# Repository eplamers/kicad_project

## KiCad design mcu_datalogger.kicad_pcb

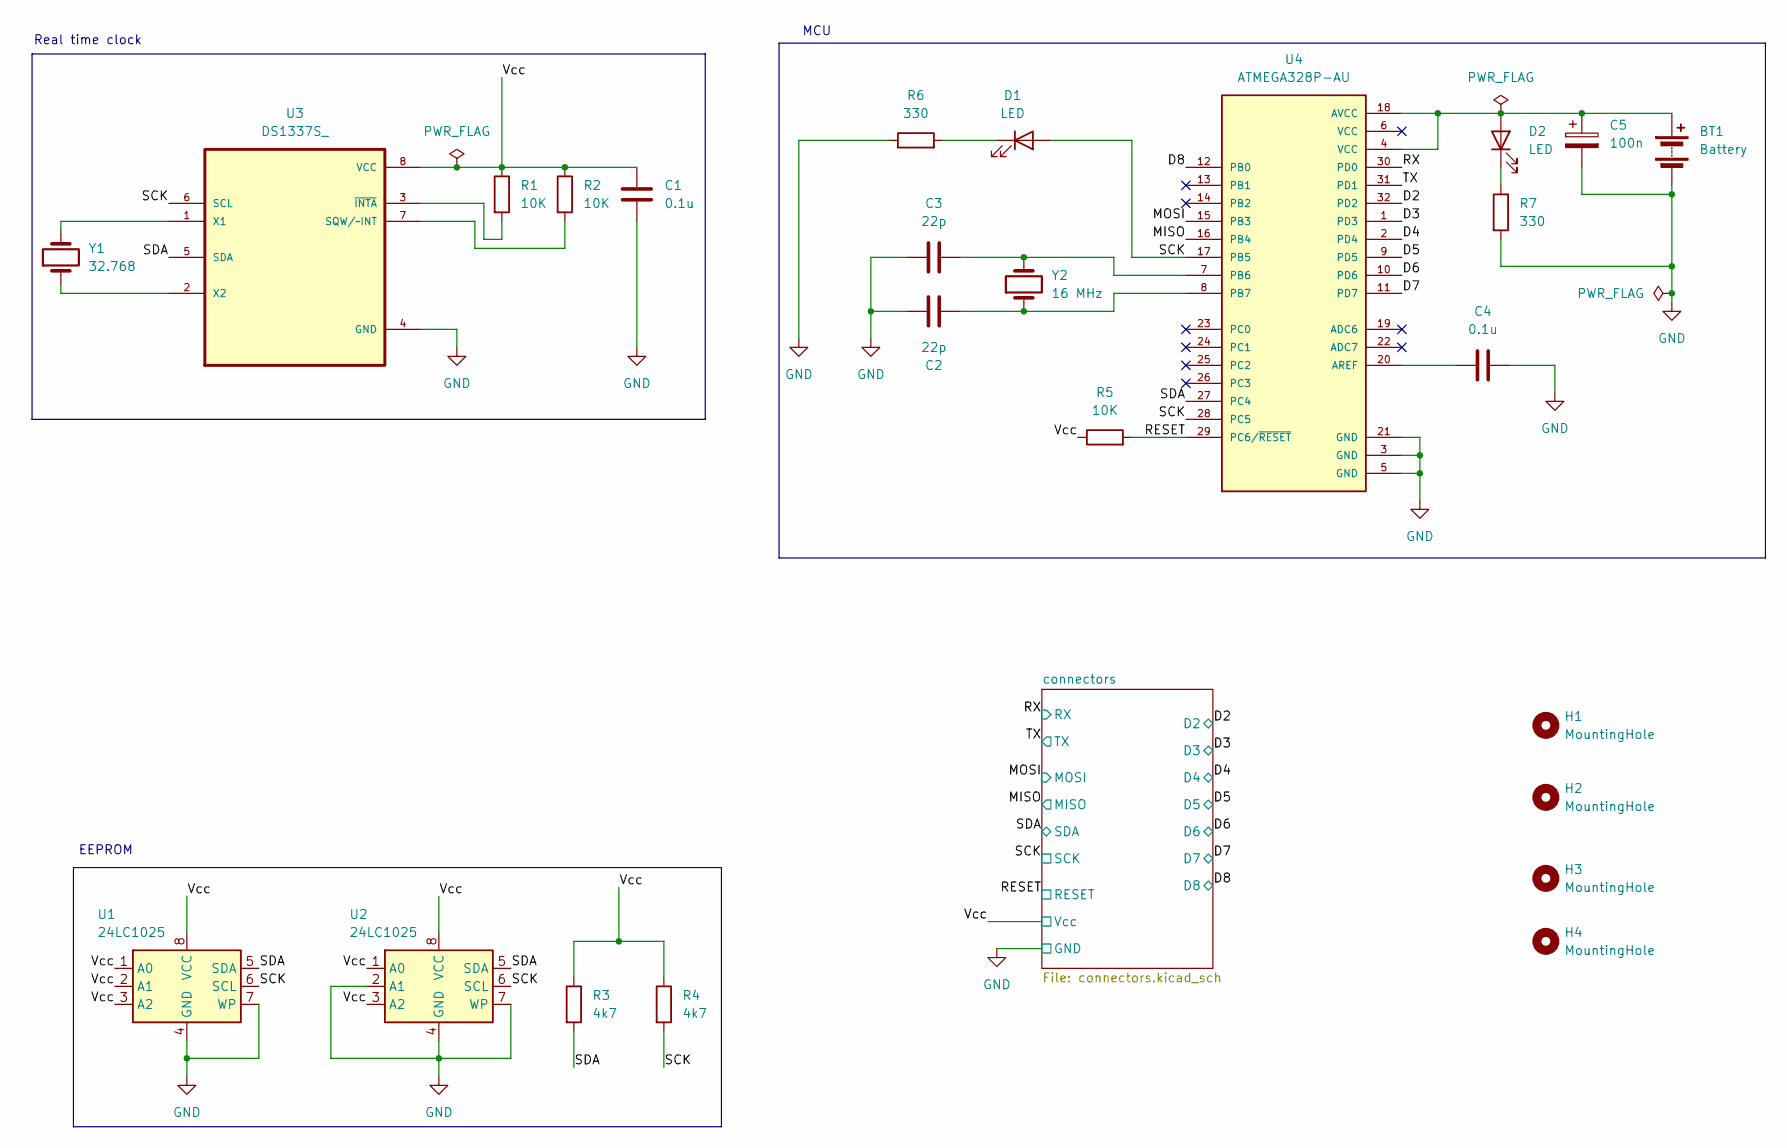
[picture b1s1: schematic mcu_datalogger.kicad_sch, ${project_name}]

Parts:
BT1: Battery; PinHeader_1x02_P2.54mm_Horizontal
C1, C4: 0.1u; C_0805_2012Metric
C2, C3: 22p; C_0805_2012Metric
C5: 100n; C_0805_2012Metric
D1, D2: LED; LED_0805_2012Metric
H1, H2, H3, H4: MountingHole; MountingHole_2.2mm_M2
R1, R2, R5: 10K; R_0805_2012Metric
R3, R4: 4k7; R_0805_2012Metric
R6, R7: 330; R_0805_2012Metric
U1, U2: 24LC1025; SOIC-8_5.3x5.3mm_P1.27mm
U3: DS1337S_; SOIC127P600X175-8N
U4: ATMEGA328P-AU; QFP80P900X900X120-32N; PARTREV 8271A
Y1: 32.768; Crystal_SMD_5032-2Pin_5.0x3.2mm_HandSoldering
Y2: 16 MHz; Crystal_SMD_5032-2Pin_5.0x3.2mm_HandSoldering

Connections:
/D2: U4.32 (PD2); also elsewhere on the board
/D3: U4.1 (PD3); also elsewhere on the board
/D4: U4.2 (PD4); also elsewhere on the board
/D5: U4.9 (PD5); also elsewhere on the board
/D6: U4.10 (PD6); also elsewhere on the board
/D7: U4.11 (PD7); also elsewhere on the board
/D8: U4.12 (PB0); also elsewhere on the board
/MISO: U4.16 (PB4); also elsewhere on the board
/MOSI: U4.15 (PB3); also elsewhere on the board
/RESET: R5.2, U4.29 (PC6/~RESET); also elsewhere on the board
/RX: U4.30 (PD0); also elsewhere on the board
/SCK: D1.2 (A), R4.2, U1.6 (SCL), U2.6 (SCL), U3.6 (SCL), U4.17 (PB5), U4.28 (PC5); also elsewhere on the board
/SDA: R3.2, U1.5 (SDA), U2.5 (SDA), U3.5 (SDA), U4.27 (PC4); also elsewhere on the board
/TX: U4.31 (PD1); also elsewhere on the board
/Vcc: C1.1, R1.1, R2.1, R3.1, R4.1, R5.1, U1.1 (A0), U1.2 (A1), U1.3 (A2), U1.8 (VCC), U2.1 (A0), U2.3 (A2), U2.8 (VCC), U3.8 (VCC); also elsewhere on the board
GND: BT1.2 (-), C1.2, C2.1, C3.1, C4.2, C5.2, R6.1, R7.2, U1.4 (GND), U1.7 (WP), U2.2 (A1), U2.4 (GND), U2.7 (WP), U3.4 (GND), U4.3 (GND), U4.5 (GND), U4.21 (GND); also elsewhere on the board
unnamed: BT1.1 (+), C5.1, D2.2 (A), U4.4 (VCC), U4.18 (AVCC)
unnamed: D1.1 (K), R6.2
unnamed: D2.1 (K), R7.1
unnamed: R2.2, U3.7 (SQW/~INT)
unnamed: U3.1 (X1), Y1.2
unnamed: U3.2 (X2), Y1.1
unnamed: R1.2, U3.3 (~INTA)
unnamed: C4.1, U4.20 (AREF)
unnamed: C3.2, U4.7 (PB6), Y2.2
unnamed: C2.2, U4.8 (PB7), Y2.1

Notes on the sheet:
MCU
EEPROM
Real time clock

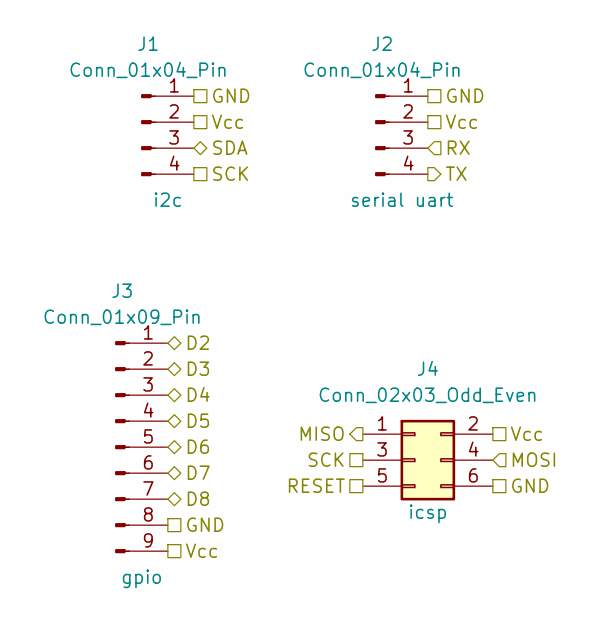
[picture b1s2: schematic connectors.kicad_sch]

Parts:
J1, J2: Conn_01x04_Pin; PinHeader_1x04_P2.54mm_Vertical
J3: Conn_01x09_Pin; PinHeader_1x09_P2.54mm_Vertical
J4: Conn_02x03_Odd_Even; PinHeader_2x03_P2.54mm_Vertical

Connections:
/D2: J3.1; also elsewhere on the board
/D3: J3.2; also elsewhere on the board
/D4: J3.3; also elsewhere on the board
/D5: J3.4; also elsewhere on the board
/D6: J3.5; also elsewhere on the board
/D7: J3.6; also elsewhere on the board
/D8: J3.7; also elsewhere on the board
/MISO: J4.1; also elsewhere on the board
/MOSI: J4.4; also elsewhere on the board
/RESET: J4.5; also elsewhere on the board
/RX: J2.3; also elsewhere on the board
/SCK: J1.4, J4.3; also elsewhere on the board
/SDA: J1.3; also elsewhere on the board
/TX: J2.4; also elsewhere on the board
/Vcc: J1.2, J2.2, J3.9, J4.2; also elsewhere on the board
GND: J1.1, J2.1, J3.8, J4.6; also elsewhere on the board

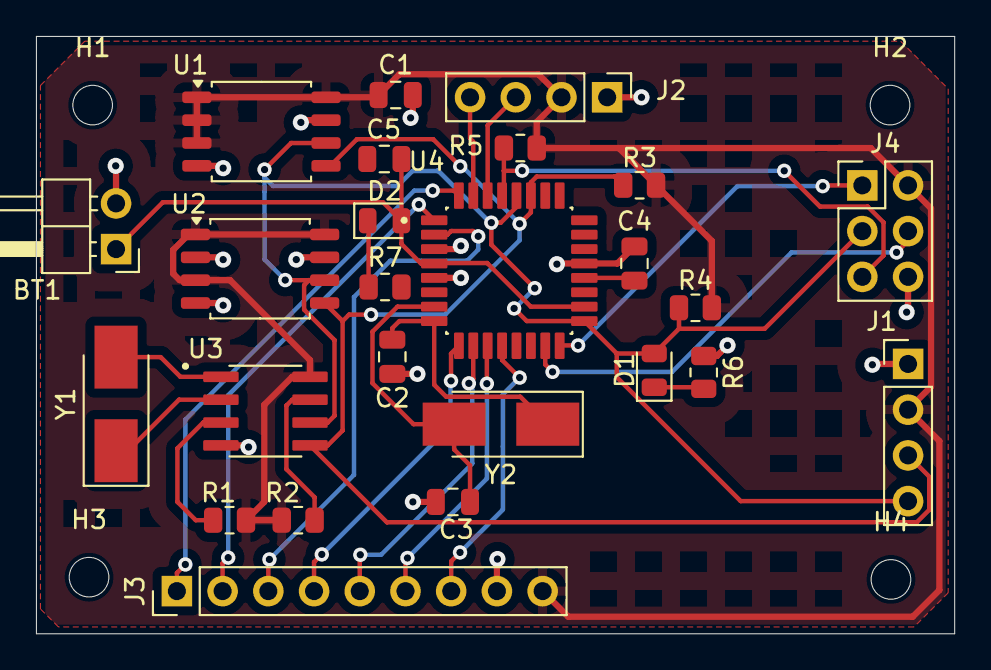
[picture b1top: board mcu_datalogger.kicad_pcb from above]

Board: 2 copper layers, 51.0 x 33.2 mm, 29 parts (0 on the bottom side), 26 nets.

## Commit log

2025-04-02 first commit of new project
2025-04-02 setup of EEschema for new project
2025-04-03 added symbols to schematic sheet
2025-04-03 added component values
2025-04-07 associated symbol & footprint
2025-04-07 wired up schematic
2025-04-08 completed wiring
2025-04-11 gave Vcc & GND power netclass label
2025-04-11 fixed ERC with 50mil grid snap
2025-04-11 added comments to schematic
2025-04-11 Setup pcbnew
2025-04-11 initiated pcbnew
2025-04-11 initial pcb layout
2025-04-29 re-arranged footprints
2025-04-29 begin routing top layer
2025-04-30 routed
2025-04-30 copper fills added
